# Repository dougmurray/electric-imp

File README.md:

# electric-imp
Compact high-accuracy impedance measuring device (LCR meter).  Features display and powered via USB.

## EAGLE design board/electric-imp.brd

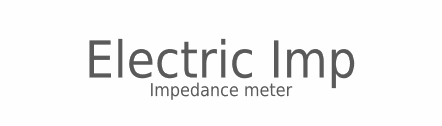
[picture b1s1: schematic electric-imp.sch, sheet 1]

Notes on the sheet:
Electric Imp
Impedance meter

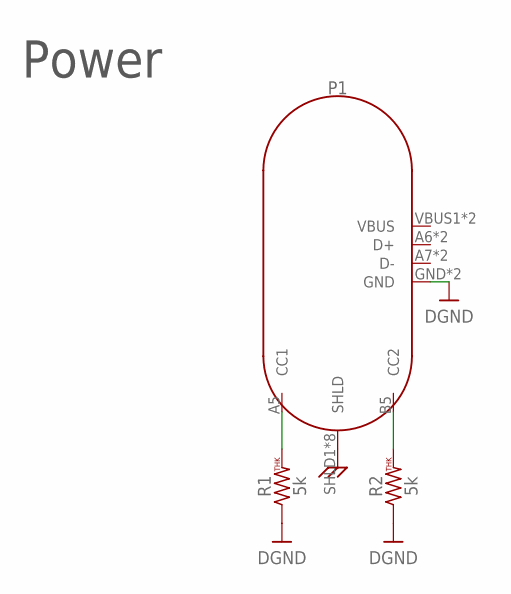
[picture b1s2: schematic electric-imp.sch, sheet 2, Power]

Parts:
P1: USB-C_2
R1, R2: 5k; 0603

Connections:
DGND: P1.GND, P1.GND2 (GND), R1.1, R2.1
SHIELD: P1.SHLD1 (SHLD), P1.SHLD2 (SHLD), P1.SHLD3 (SHLD), P1.SHLD4 (SHLD), P1.SHLD5 (SHLD), P1.SHLD6 (SHLD), P1.SHLD7 (SHLD), P1.SHLD8 (SHLD)
UCPD1_CC1: P1.A5 (CC1), R1.2
UCPD1_CC2: P1.B5 (CC2), R2.2

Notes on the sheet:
Power

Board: 4 copper layers, 3 parts (0 on the bottom side), 4 nets, no tracks yet.

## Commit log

2021-11-09 Added docs for references and start of blank board.
2021-11-09 Added paper on impedance measuring to docs.
2021-11-17 Start of impedance measure circuit.
